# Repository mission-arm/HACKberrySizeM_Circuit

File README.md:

# HACKberrySizeM_Circuit

This repository contains circuit design of middle sized [HACKberry](https://github.com/mission-arm/HACKberry).

## Licenses

The electrical circuit design of [HACKberry](https://github.com/mission-arm/HACKberry) by [Exiii](info@exiii.jp) is licensed under [Creative Commons License BY-NC-SA 4.0 International](https://creativecommons.org/licenses/by-nc-sa/4.0/).
( Please refer to chapter 3.1 in [Original HACKberry Lincense](https://github.com/mission-arm/HACKberry) for detail. )

And This electrical circuit design of  middle sized HACKberry ) is a derivative of HACKberry and is licensed under [Creative Commons License BY-NC-SA 4.0 International](https://creativecommons.org/licenses/by-nc-sa/4.0/) by MissionARMJapan.

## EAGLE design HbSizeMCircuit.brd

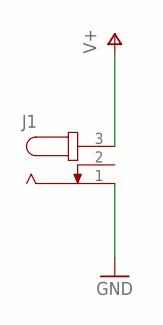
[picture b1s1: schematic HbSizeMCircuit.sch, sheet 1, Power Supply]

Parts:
J1: JACK-PLUG1; SPC4078

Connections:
GND: J1.1; also elsewhere on the board
V+: J1.3; also elsewhere on the board

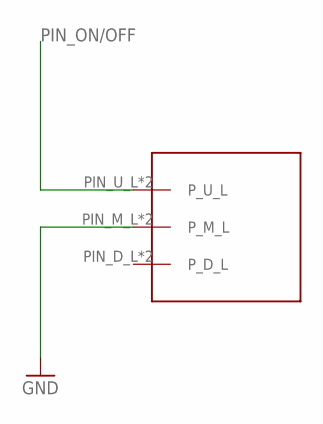
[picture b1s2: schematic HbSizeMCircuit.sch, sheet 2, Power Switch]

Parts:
U$2: IS-1250_POWERSWITCH

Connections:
GND: U$2.PIN_M_L (P_M_L), U$2.PIN_M_R (P_M_L); also elsewhere on the board
PIN_ON/OFF: U$2.PIN_U_L (P_U_L), U$2.PIN_U_R (P_U_L); also elsewhere on the board

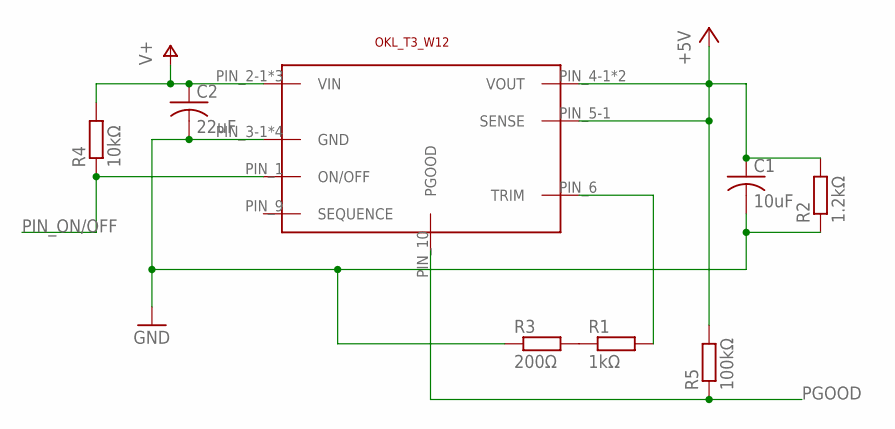
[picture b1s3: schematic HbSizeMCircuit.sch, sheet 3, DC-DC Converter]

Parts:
C1: 10uF; C1206
C2: 22uF; C1206
R1: 1kΩ; M1206
R2: 1.2kΩ; M1206
R3: 200Ω; M1206
R4: 10kΩ; R1206
R5: 100kΩ; M1206
U$8: OKL_T3_W12

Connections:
+5V: C1.1, R2.2, R5.2, U$8.PIN_4-1 (VOUT), U$8.PIN_4-2 (VOUT), U$8.PIN_5-1 (SENSE); also elsewhere on the board
GND: C1.2, C2.2, R2.1, R3.1, U$8.PIN_3-1 (GND), U$8.PIN_3-2 (GND), U$8.PIN_3-3 (GND), U$8.PIN_7 (GND); also elsewhere on the board
unnamed: R1.2, U$8.PIN_6 (TRIM)
unnamed: R1.1, R3.2
PGOOD: R5.1, U$8.PIN_10 (PGOOD); also elsewhere on the board
PIN_ON/OFF: R4.1, U$8.PIN_1 (ON/OFF); also elsewhere on the board
V+: C2.1, R4.2, U$8.PIN_2-1 (VIN), U$8.PIN_2-2 (VIN), U$8.PIN_2-3 (VIN); also elsewhere on the board

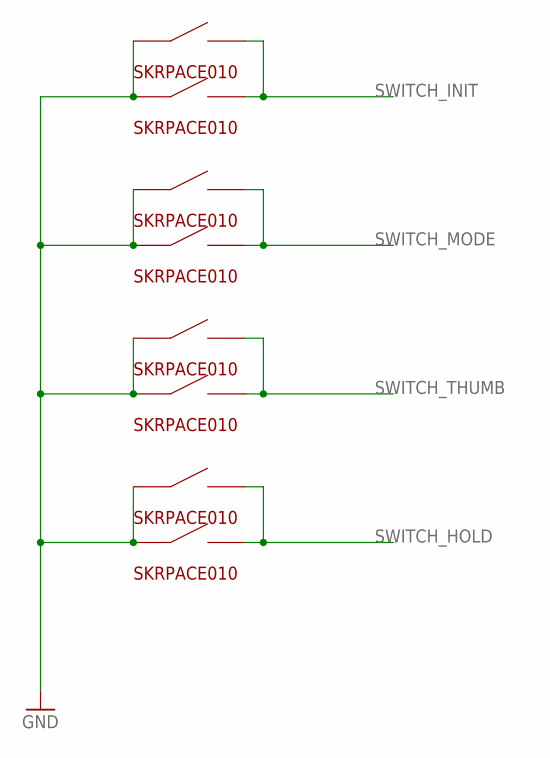
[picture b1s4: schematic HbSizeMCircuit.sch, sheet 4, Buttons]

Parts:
U$1, U$3, U$4, U$5, U$12, U$13, U$14, U$15: SKRPACE010

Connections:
GND: U$1.PINA_LEFT (A_LEFT), U$1.PINA_RIGHT (A_LEFT), U$3.PINA_LEFT (A_LEFT), U$3.PINA_RIGHT (A_LEFT), U$4.PINA_LEFT (A_LEFT), U$4.PINA_RIGHT (A_LEFT), U$5.PINA_LEFT (A_LEFT), U$5.PINA_RIGHT (A_LEFT), U$12.PINA_LEFT (A_LEFT), U$12.PINA_RIGHT (A_LEFT), U$13.PINA_LEFT (A_LEFT), U$13.PINA_RIGHT (A_LEFT), U$14.PINA_LEFT (A_LEFT), U$14.PINA_RIGHT (A_LEFT), U$15.PINA_LEFT (A_LEFT), U$15.PINA_RIGHT (A_LEFT); also elsewhere on the board
SWITCH_HOLD: U$12.PINB_LEFT (B_LEFT), U$12.PINB_RIGHT (B_LEFT), U$15.PINB_LEFT (B_LEFT), U$15.PINB_RIGHT (B_LEFT); also elsewhere on the board
SWITCH_INIT: U$1.PINB_LEFT (B_LEFT), U$1.PINB_RIGHT (B_LEFT), U$5.PINB_LEFT (B_LEFT), U$5.PINB_RIGHT (B_LEFT); also elsewhere on the board
SWITCH_MODE: U$3.PINB_LEFT (B_LEFT), U$3.PINB_RIGHT (B_LEFT), U$13.PINB_LEFT (B_LEFT), U$13.PINB_RIGHT (B_LEFT); also elsewhere on the board
SWITCH_THUMB: U$4.PINB_LEFT (B_LEFT), U$4.PINB_RIGHT (B_LEFT), U$14.PINB_LEFT (B_LEFT), U$14.PINB_RIGHT (B_LEFT); also elsewhere on the board

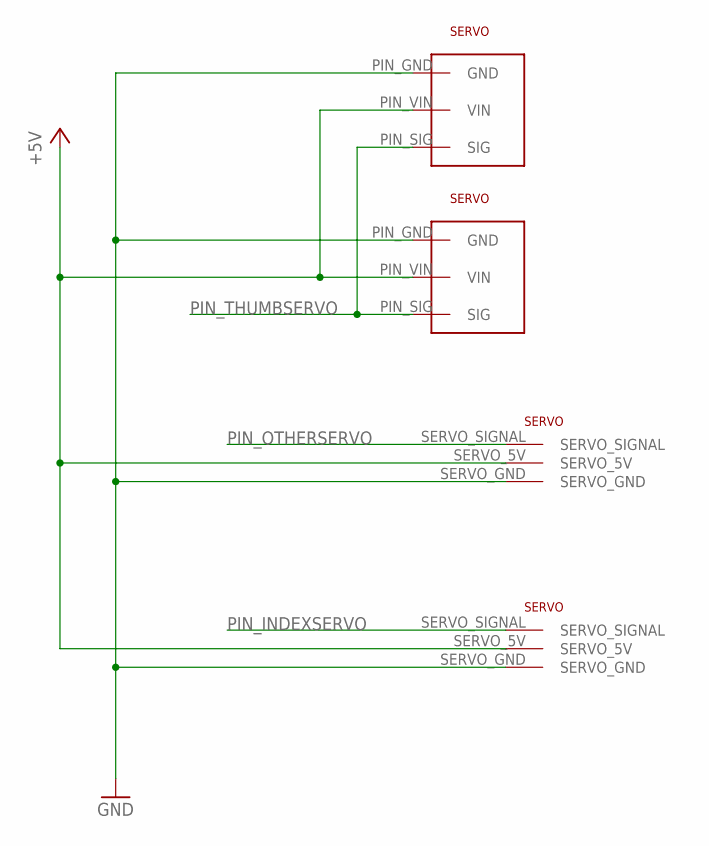
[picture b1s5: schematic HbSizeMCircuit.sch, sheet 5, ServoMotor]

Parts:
U$7, U$11: NN_SERVO
U$9, U$16: 53398-0371

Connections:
+5V: U$7.SERVO_5V, U$9.PIN_VIN (VIN), U$11.SERVO_5V, U$16.PIN_VIN (VIN); also elsewhere on the board
GND: U$7.SERVO_GND, U$9.PIN_GND (GND), U$11.SERVO_GND, U$16.PIN_GND (GND); also elsewhere on the board
PIN_INDEXSERVO: U$11.SERVO_SIGNAL; also elsewhere on the board
PIN_OTHERSERVO: U$7.SERVO_SIGNAL; also elsewhere on the board
PIN_THUMBSERVO: U$9.PIN_SIG (SIG), U$16.PIN_SIG (SIG); also elsewhere on the board

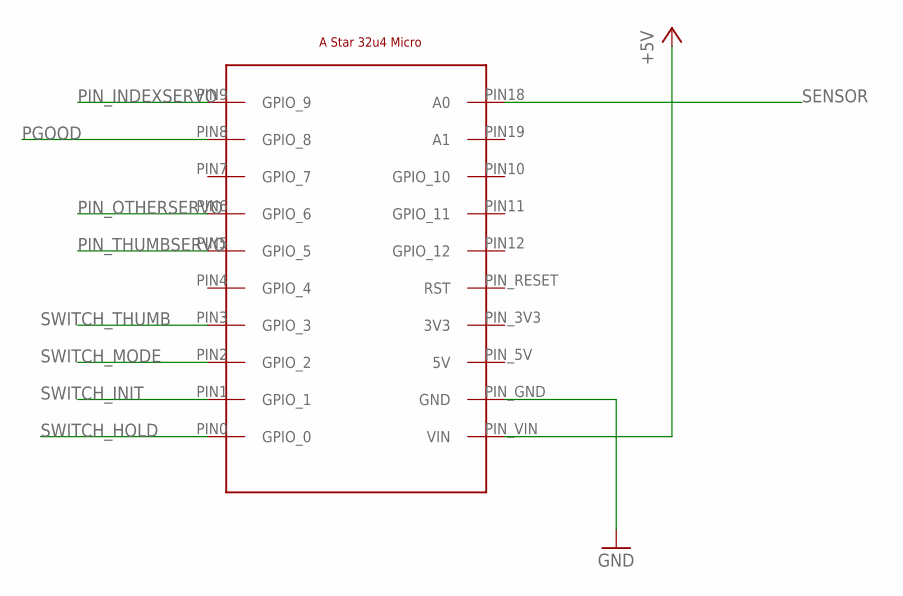
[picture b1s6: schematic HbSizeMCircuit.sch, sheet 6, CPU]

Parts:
U$6: POLOLU_A_STAR_32U4_MICRO_SMD

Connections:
+5V: U$6.PIN_VIN (VIN); also elsewhere on the board
GND: U$6.PIN_GND (GND); also elsewhere on the board
PGOOD: U$6.PIN8 (GPIO_8); also elsewhere on the board
PIN_INDEXSERVO: U$6.PIN9 (GPIO_9); also elsewhere on the board
PIN_OTHERSERVO: U$6.PIN6 (GPIO_6); also elsewhere on the board
PIN_THUMBSERVO: U$6.PIN5 (GPIO_5); also elsewhere on the board
SENSOR: U$6.PIN18 (A0); also elsewhere on the board
SWITCH_HOLD: U$6.PIN0 (GPIO_0); also elsewhere on the board
SWITCH_INIT: U$6.PIN1 (GPIO_1); also elsewhere on the board
SWITCH_MODE: U$6.PIN2 (GPIO_2); also elsewhere on the board
SWITCH_THUMB: U$6.PIN3 (GPIO_3); also elsewhere on the board

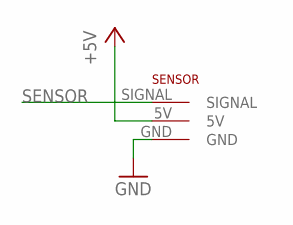
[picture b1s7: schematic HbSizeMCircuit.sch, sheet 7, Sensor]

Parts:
U$10: NN_SENSOR

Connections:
+5V: U$10.5V; also elsewhere on the board
GND: U$10.GND; also elsewhere on the board
SENSOR: U$10.SIGNAL; also elsewhere on the board

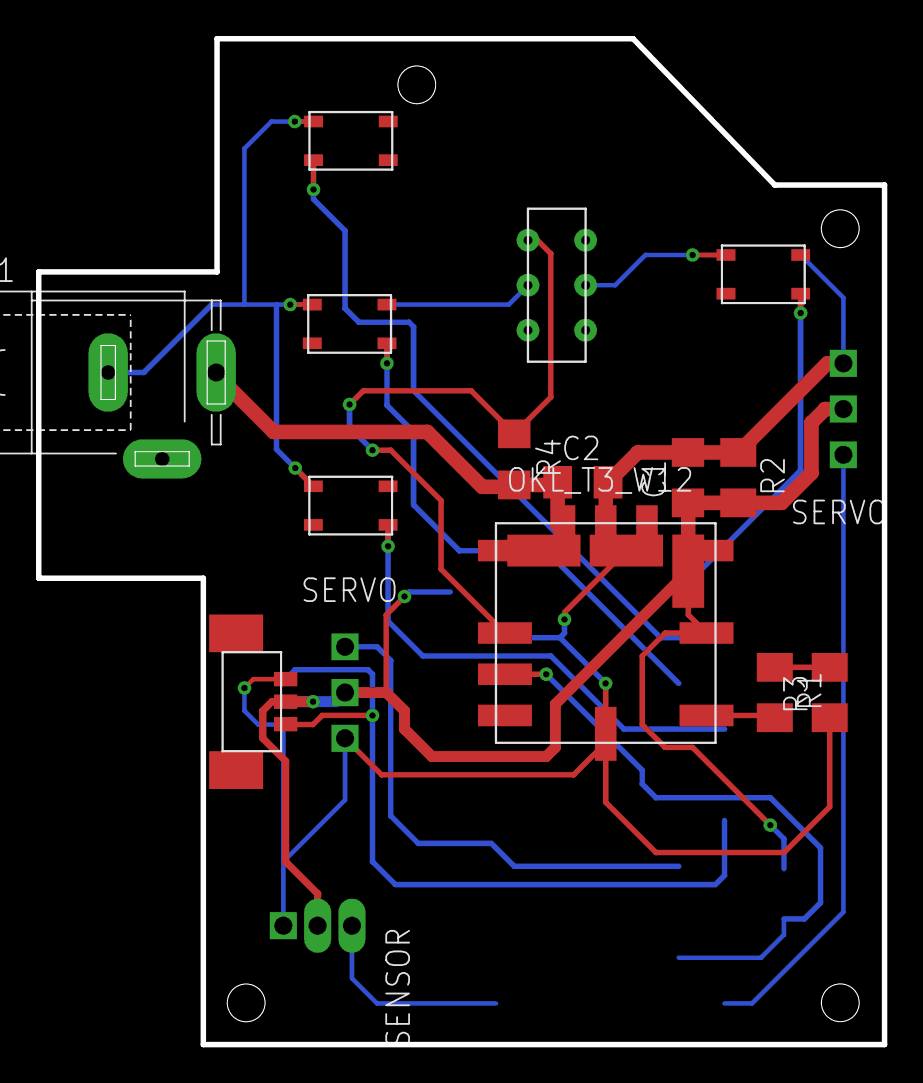
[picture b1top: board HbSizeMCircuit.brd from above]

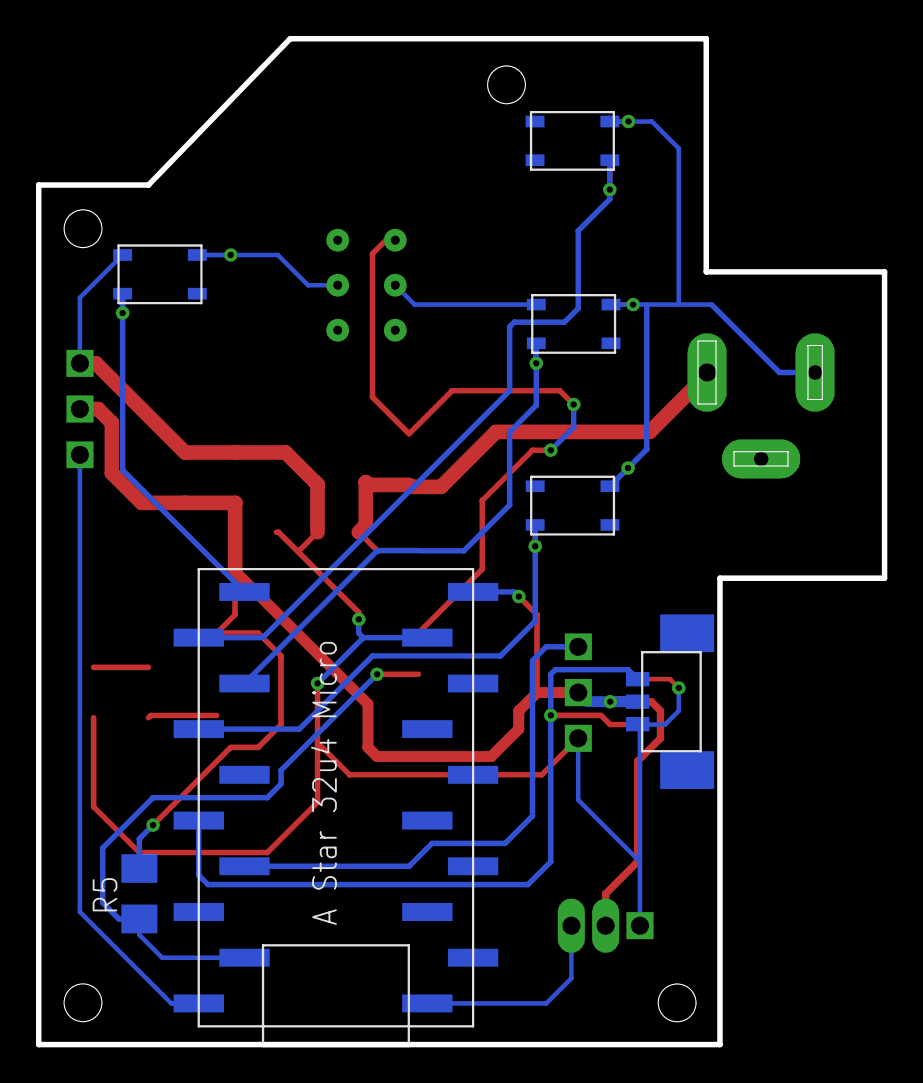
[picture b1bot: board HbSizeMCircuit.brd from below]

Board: 2 copper layers, 47.0 x 55.9 mm, 24 parts (7 on the bottom side), 15 nets.

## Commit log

2018-03-09 add gitignore
2018-03-09 add schematics and board layout
2018-03-14 DCジャックを変更
